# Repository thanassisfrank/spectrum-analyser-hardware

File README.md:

# 5.8GHz Spectrum analyser hardware

This is an open source project to create a device for analysing the 5.8GHz radio band using the RX5808 analog receiver module and the ESP32-C3 Zero. This repository holds the hardware for the device created with KiCad. For an overview of the firmware, please see *firmware repo*.

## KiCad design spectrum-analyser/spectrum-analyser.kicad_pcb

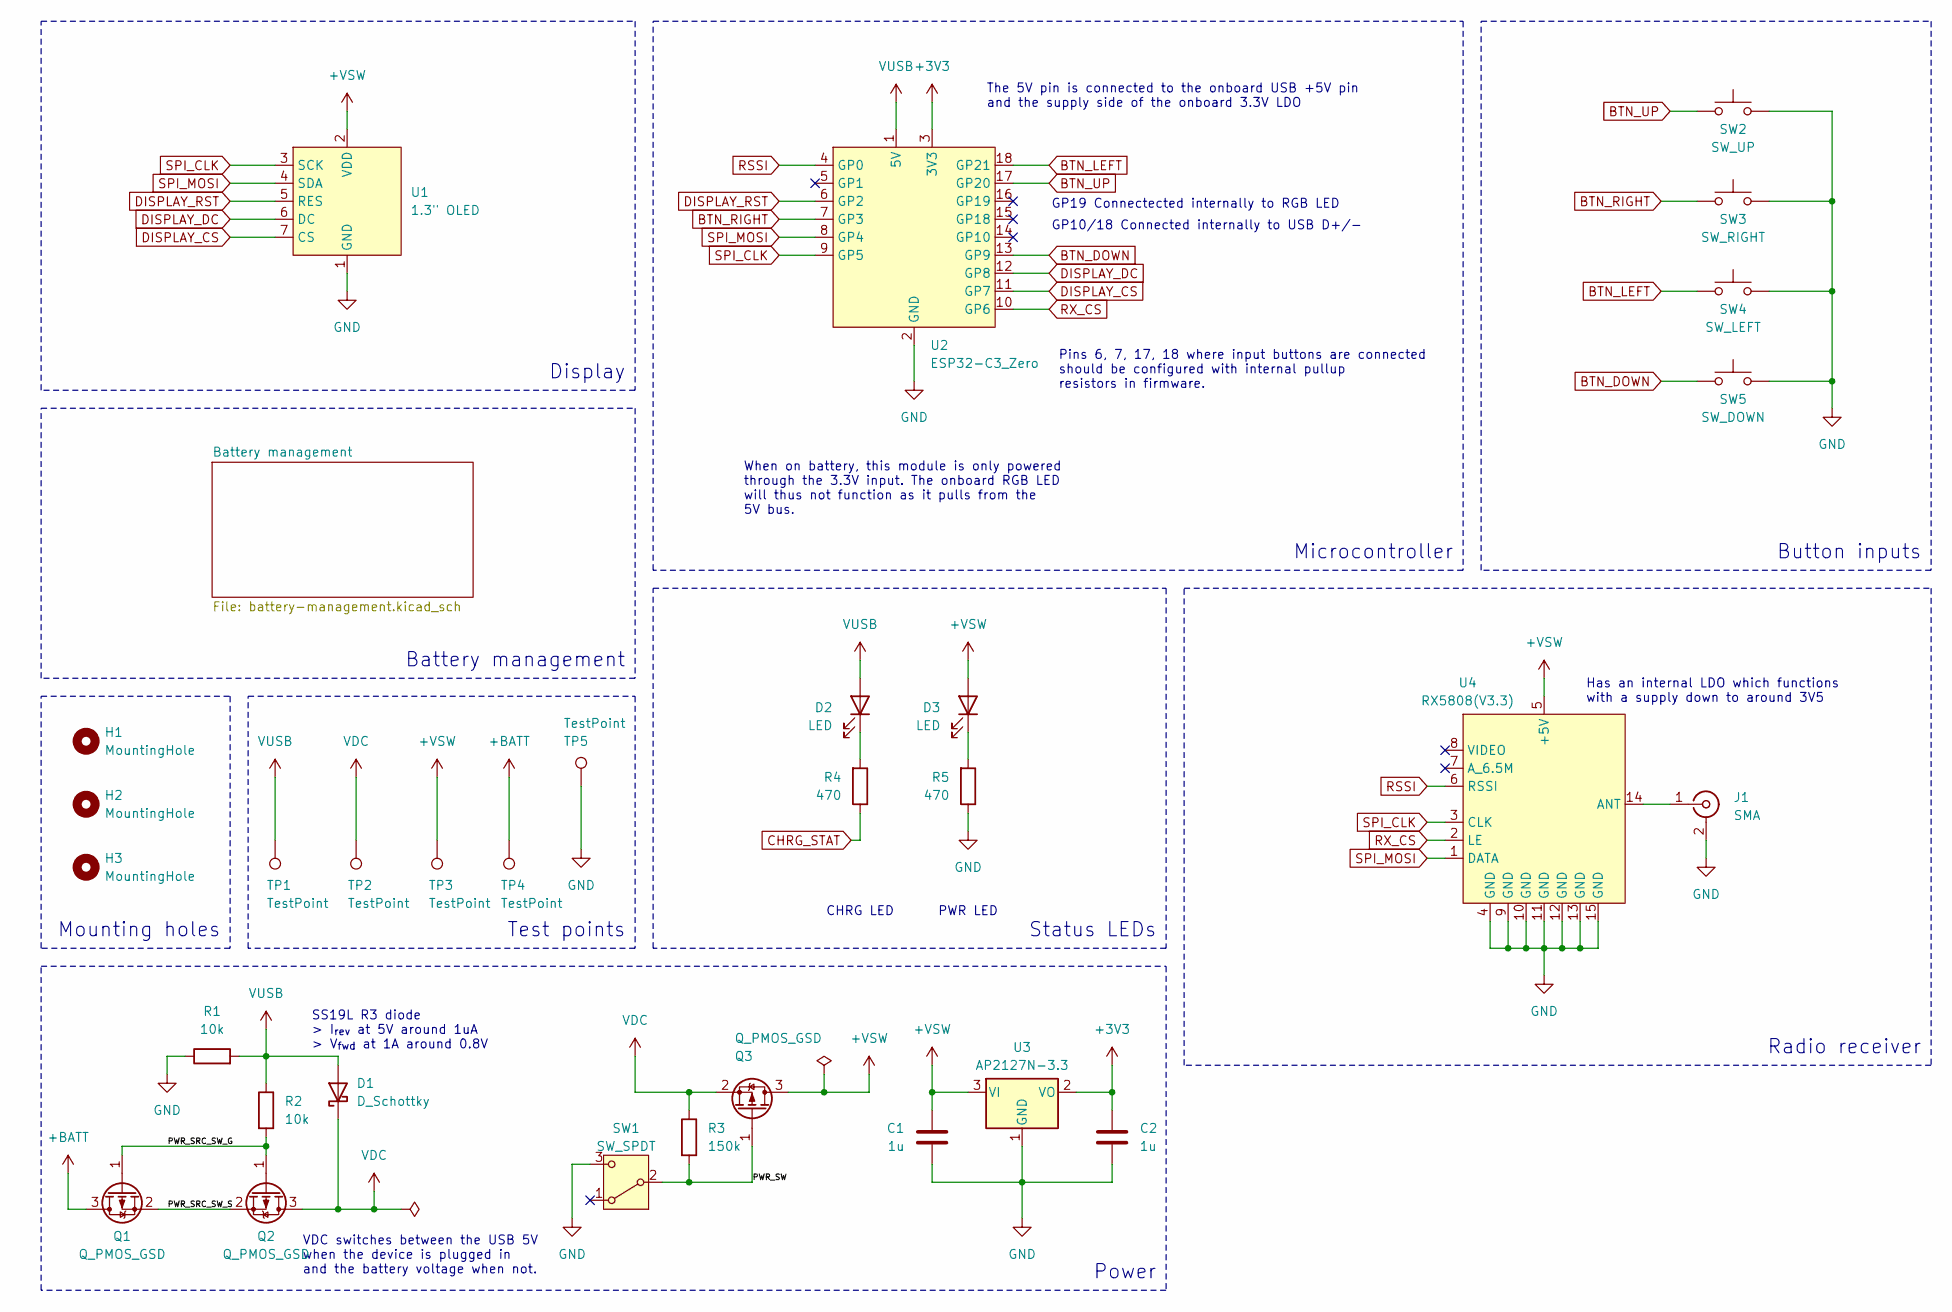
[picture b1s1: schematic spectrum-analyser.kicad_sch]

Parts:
C1, C2: 1u; C_0603_1608Metric_Pad1.08x0.95mm_HandSolder
D1: D_Schottky; D_SMA_Handsoldering
D2, D3: LED; LED_0603_1608Metric_Pad1.05x0.95mm_HandSolder
H1, H2, H3: MountingHole; MountingHole_3.2mm_M3_ISO7380
J1: SMA; SMA_Samtec_SMA-J-P-H-ST-EM1_EdgeMount
Q1, Q2, Q3: Q_PMOS_GSD; SOT-23
R1, R2: 10k; R_0603_1608Metric_Pad0.98x0.95mm_HandSolder
R3: 150k; R_0603_1608Metric_Pad0.98x0.95mm_HandSolder
R4, R5: 470; R_0603_1608Metric_Pad0.98x0.95mm_HandSolder
SW1: SW_SPDT; SW_SPDT_TEC_1825232-1
SW2: SW_UP; SW_PUSH_ADAFRUIT_SMALL
SW3: SW_RIGHT; SW_PUSH_ADAFRUIT_SMALL
SW4: SW_LEFT; SW_PUSH_ADAFRUIT_SMALL
SW5: SW_DOWN; SW_PUSH_ADAFRUIT_SMALL
TP1, TP2, TP3, TP4: TestPoint; TestPoint_Pad_D2.0mm
TP5: TestPoint; TestPoint_THTPad_D2.0mm_Drill1.0mm
U1: 1.3" OLED; 1.30 OLED
U2: ESP32-C3_Zero
U3: AP2127N-3.3; SOT-23
U4: RX5808(V3.3)

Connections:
+3V3: C2.1, U2.3 (3V3), U3.2 (VO)
+BATT: Q1.3 (D), TP4.1; also elsewhere on the board
+VSW: C1.1, D3.2 (A), Q3.3 (D), TP3.1, U1.2 (VDD), U3.3 (VI), U4.5 (+5V)
/PWR_SRC_SW_G: Q1.1 (G), Q2.1 (G), R2.2
/PWR_SRC_SW_S: Q1.2 (S), Q2.2 (S)
/PWR_SW: Q3.1 (G), R3.2, SW1.2 (B)
BTN_DOWN: SW5.1, U2.13 (GP9)
BTN_LEFT: SW4.1, U2.18 (GP21)
BTN_RIGHT: SW3.1, U2.7 (GP3)
BTN_UP: SW2.1, U2.17 (GP20)
CHRG_STAT: R4.1; also elsewhere on the board
DISPLAY_CS: U1.7 (CS), U2.11 (GP7)
DISPLAY_DC: U1.6 (DC), U2.12 (GP8)
DISPLAY_RST: U1.5 (RES), U2.6 (GP2)
GND: C1.2, C2.2, J1.2 (Ext), R1.1, R5.1, SW1.3 (C), SW2.2, SW3.2, SW4.2, SW5.2, TP5.1, U1.1 (GND), U2.2 (GND), U3.1 (GND), U4.4 (GND), U4.9 (GND), U4.10 (GND), U4.11 (GND), U4.12 (GND), U4.13 (GND), U4.15 (GND); also elsewhere on the board
unnamed: D2.1 (K), R4.2
unnamed: D3.1 (K), R5.2
unnamed: J1.1 (In), U4.14 (ANT)
RSSI: U2.4 (GP0), U4.6 (RSSI)
RX_CS: U2.10 (GP6), U4.2 (LE)
SPI_CLK: U1.3 (SCK), U2.9 (GP5), U4.3 (CLK)
SPI_MOSI: U1.4 (SDA), U2.8 (GP4), U4.1 (DATA)
VDC: D1.1 (K), Q2.3 (D), Q3.2 (S), R3.1, TP2.1
VUSB: D1.2 (A), D2.2 (A), R1.2, R2.1, TP1.1, U2.1 (5V); also elsewhere on the board

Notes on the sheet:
VDC switches between the USB 5V when the device is plugged in and the battery voltage when not.
Power
PWR LED
GP10/18 Connected internally to USB D+/-
Pins 6, 7, 17, 18 where input buttons are connected should be configured with internal pullup resistors in firmware.
When on battery, this module is only powered through the 3.3V input. The onboard RGB LED will thus not function as it pulls from the 5V bus.
Button inputs
Status LEDs
Has an internal LDO which functions with a supply down to around 3V5
Battery management
GP19 Connectected internally to RGB LED
Radio receiver
Test points
Microcontroller
The 5V pin is connected to the onboard USB +5V pin and the supply side of the onboard 3.3V LDO
SS19L R3 diode > I_{rev} at 5V around 1uA > V_{fwd} at 1A around 0.8V
CHRG LED
Mounting holes
Display

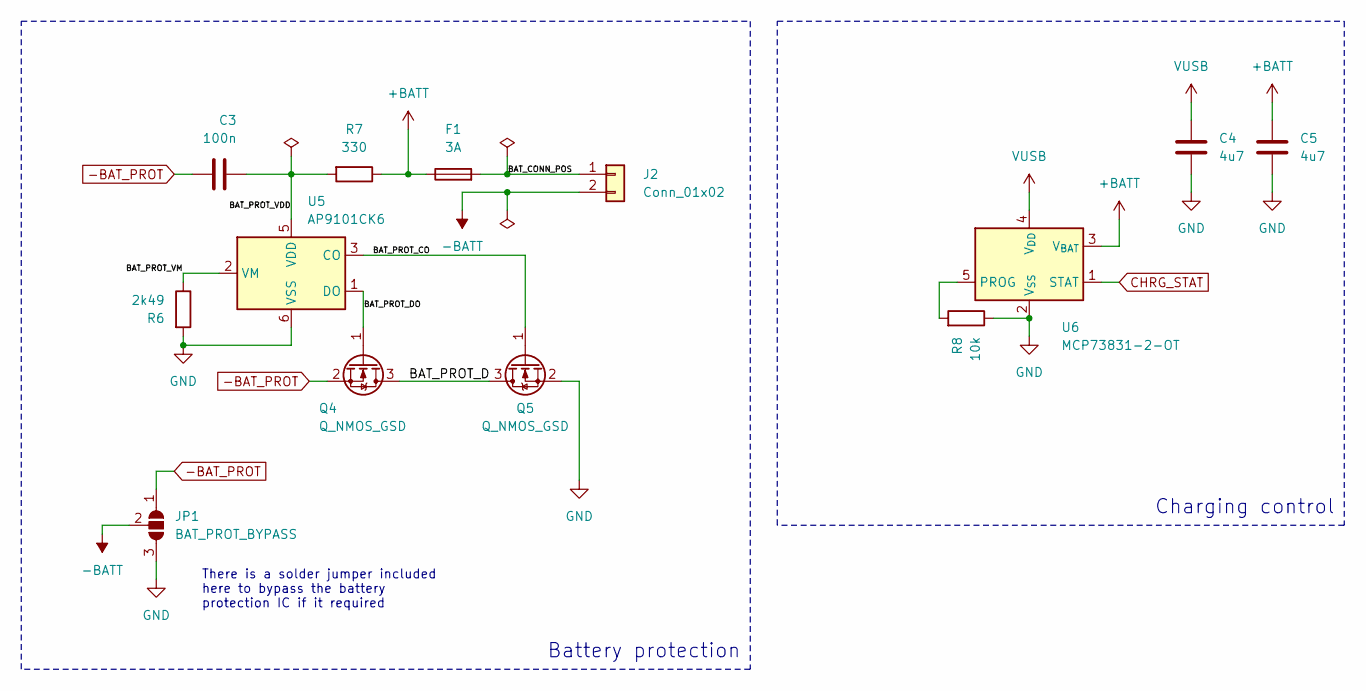
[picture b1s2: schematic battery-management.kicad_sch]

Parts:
C3: 100n; C_0603_1608Metric_Pad1.08x0.95mm_HandSolder
C4, C5: 4u7; C_0603_1608Metric_Pad1.08x0.95mm_HandSolder
F1: 3A; Fuse_0603_1608Metric_Pad1.05x0.95mm_HandSolder
J2: Conn_01x02; PinHeader_1x02_P2.54mm_Vertical
JP1: BAT_PROT_BYPASS; SolderJumper-3_P1.3mm_Open_RoundedPad1.0x1.5mm
Q4, Q5: Q_NMOS_GSD; SOT-23
R6: 2k49; R_0603_1608Metric_Pad0.98x0.95mm_HandSolder
R7: 330; R_0603_1608Metric_Pad0.98x0.95mm_HandSolder
R8: 10k; R_0603_1608Metric_Pad0.98x0.95mm_HandSolder
U5: AP9101CK6; SOT-23-6
U6: MCP73831-2-OT; SOT-23-5

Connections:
+BATT: C5.1, F1.1, R7.1, U6.3 (V_{BAT}); also elsewhere on the board
-BATT: J2.2, JP1.2 (C)
-BAT_PROT: C3.1, JP1.1 (A), Q4.2 (S)
/Battery management/BAT_CONN_POS: F1.2, J2.1
/Battery management/BAT_PROT_CO: Q5.1 (G), U5.3 (CO)
/Battery management/BAT_PROT_D: Q4.3 (D), Q5.3 (D)
/Battery management/BAT_PROT_DO: Q4.1 (G), U5.1 (DO)
/Battery management/BAT_PROT_VDD: C3.2, R7.2, U5.5 (VDD)
/Battery management/BAT_PROT_VM: R6.1, U5.2 (VM)
CHRG_STAT: U6.1 (STAT); also elsewhere on the board
GND: C4.2, C5.2, JP1.3 (B), Q5.2 (S), R6.2, R8.1, U5.6 (VSS), U6.2 (V_{SS}); also elsewhere on the board
unnamed: R8.2, U6.5 (PROG)
VUSB: C4.1, U6.4 (V_{DD}); also elsewhere on the board

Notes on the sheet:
Charging control
There is a solder jumper included here to bypass the battery protection IC if it required
Battery protection

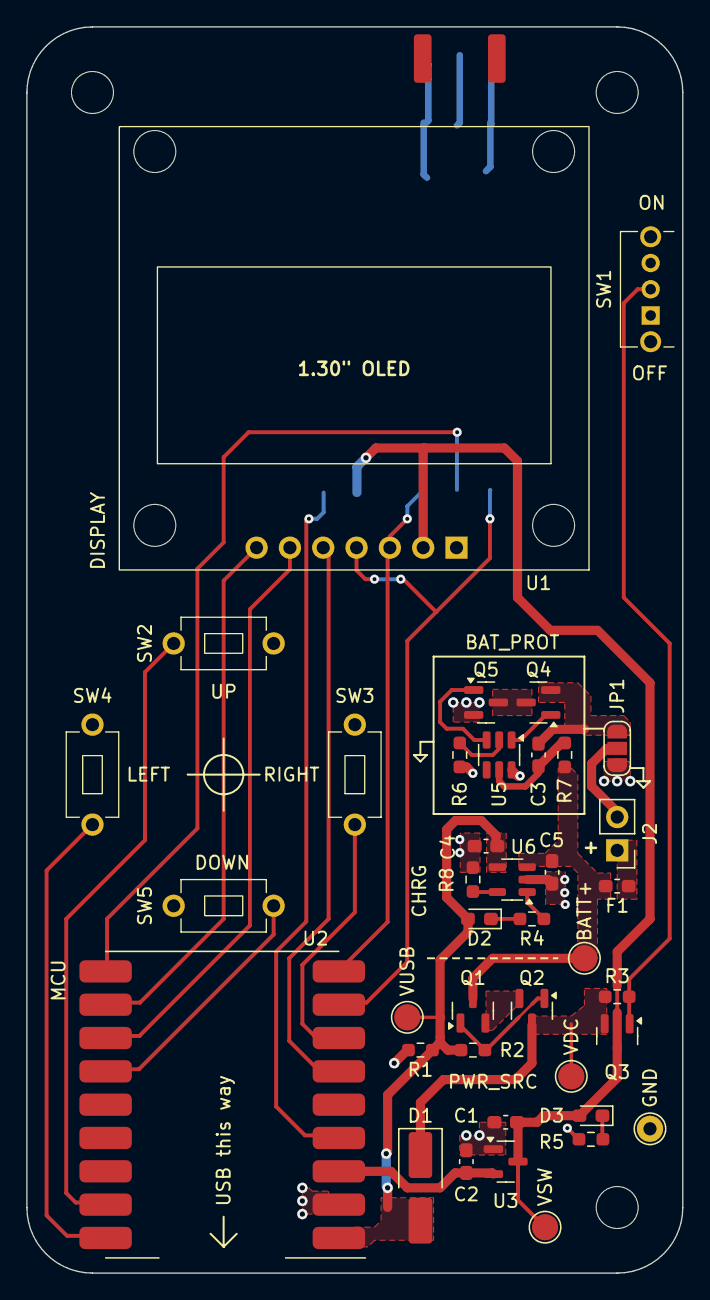
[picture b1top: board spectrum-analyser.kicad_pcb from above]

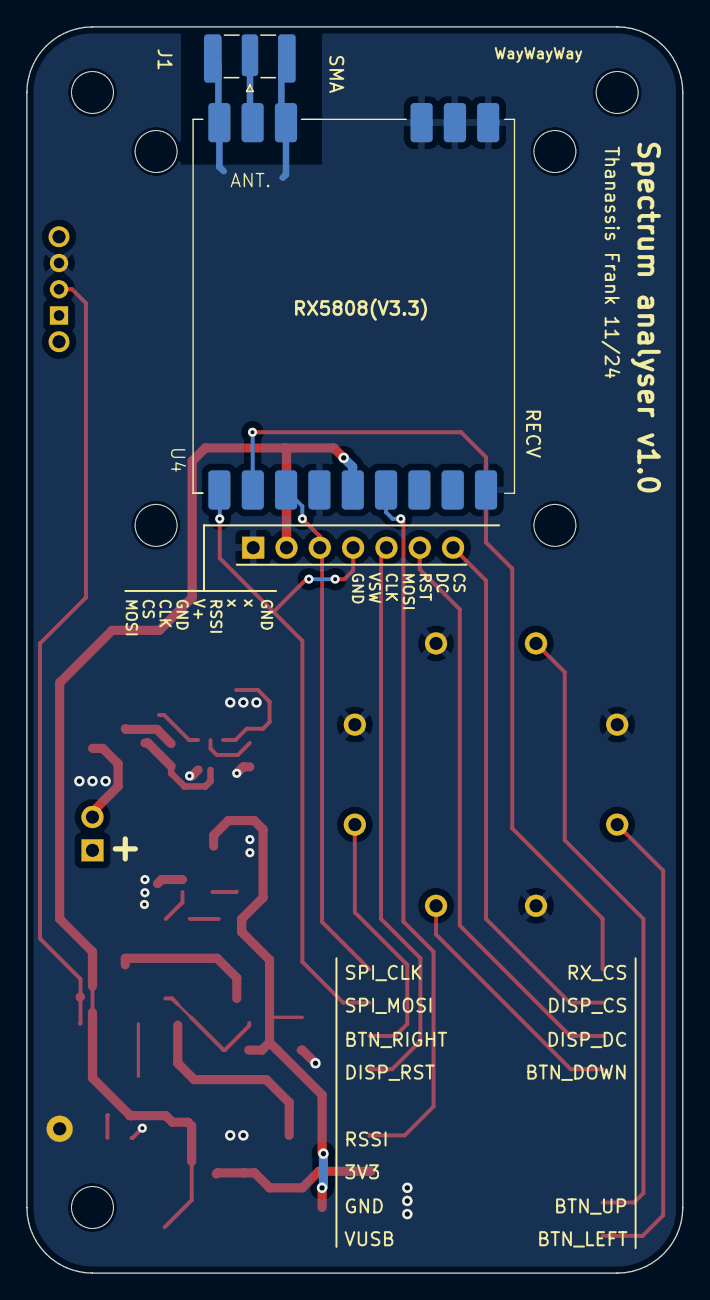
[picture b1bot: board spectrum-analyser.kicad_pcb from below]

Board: 2 copper layers, 50.0 x 95.0 mm, 44 parts (2 on the bottom side), 33 nets.

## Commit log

2024-10-16 Create KiCad files
2024-10-16 Format schematic sheet
2024-10-18 Add power and battery charge management to schematic
2024-10-20 Add battery protection and modify power delivery
2024-10-26 Assign component footprints
2024-10-27 Start initial PCB layout
2024-10-27 Improve PCB layout
2024-10-28 Add mounting holes
2024-10-28 Improve component layout for spacing and round mechanical positions
2024-10-30 Modify layout to group power and battery, increase board length by 5mm
2024-11-06 Add GND keepout around SMA and adjust thermal relief spoke angle for RX module
2024-11-10 Route the power management sections
2024-11-10 Route signal traces and adjust mcu module pin assignment
2024-11-18 Add informational silkscreen and change 3v3 LDO package
2024-11-19 Assign component values and add charger capacitors
2024-11-20 Re-organise battery management sections
2024-11-20 Polish silkscreen and power switch layout
2024-11-21 Adjust button placement
2024-11-21 Add Batt+ test point
2024-11-21 Generate manufacturing files
